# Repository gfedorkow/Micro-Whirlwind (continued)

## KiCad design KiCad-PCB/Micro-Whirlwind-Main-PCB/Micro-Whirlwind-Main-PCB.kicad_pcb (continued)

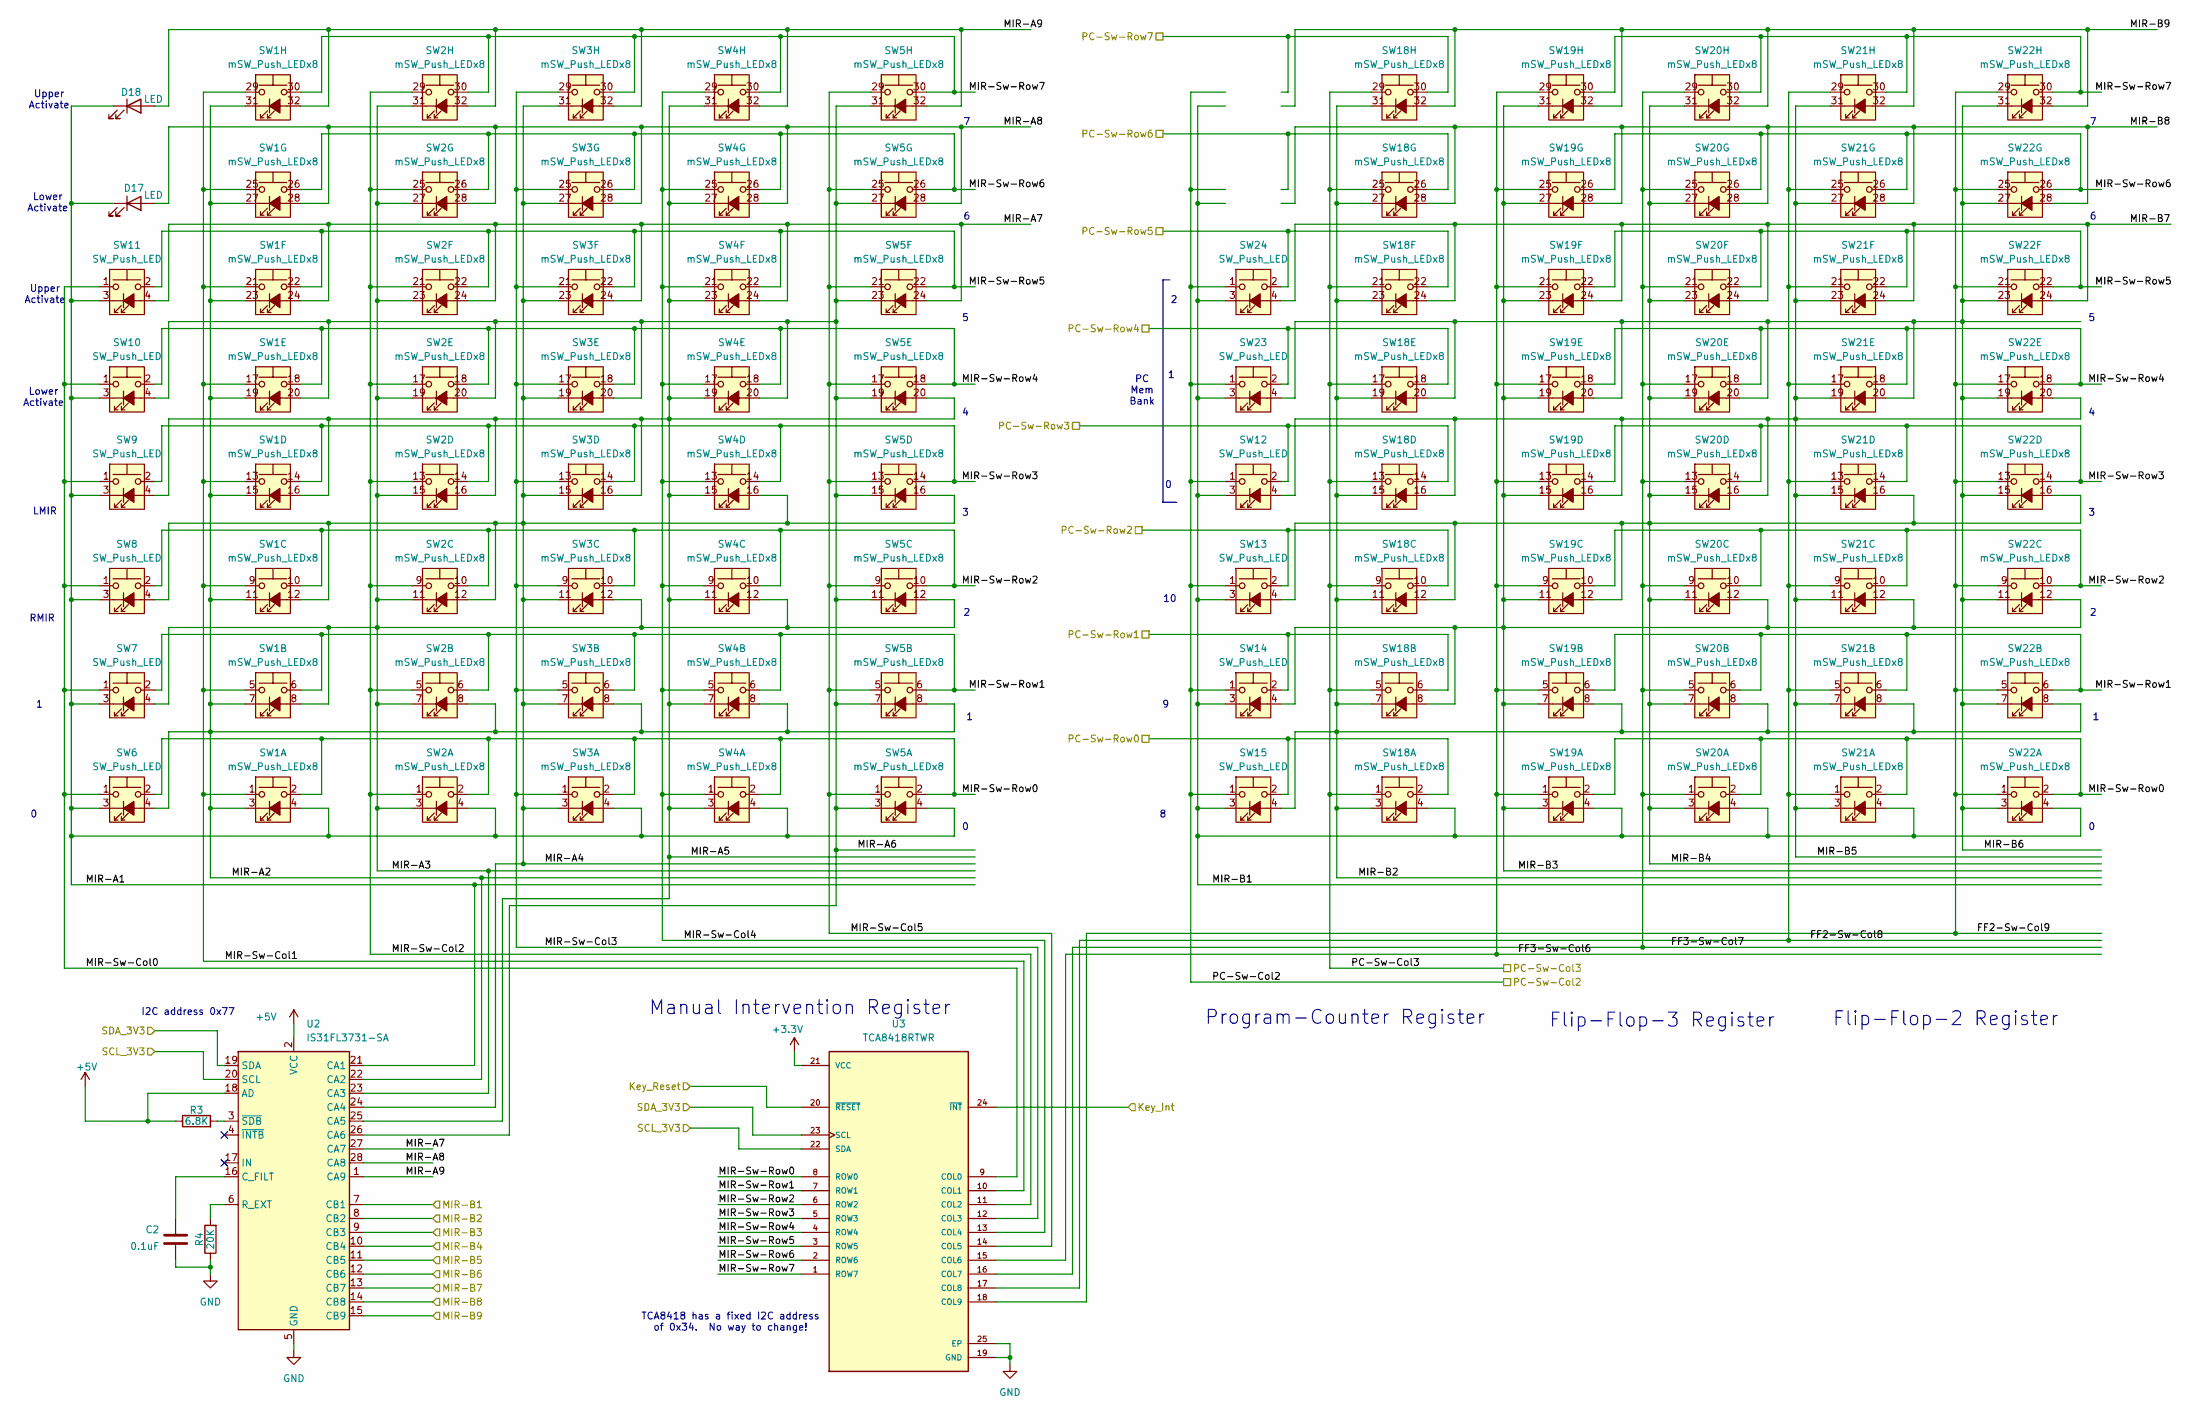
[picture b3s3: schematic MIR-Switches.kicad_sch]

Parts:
C2: 0.1uF; Null-FootPrint
D17, D18: LED; LED_D3.0mm_panel_cut
R3: 6.8K; Null-FootPrint
R4: 20K; Null-FootPrint
SW1, SW2, SW3, SW4, SW5, SW18, SW19, SW20, SW21, SW22: mSW_Push_LEDx8; Null-FootPrint
SW6, SW7, SW8, SW9, SW12, SW13, SW14, SW15, SW23, SW24: SW_Push_LED; Null-FootPrint
SW10, SW11: SW_Push_LED; ILS-TB-140-SW_PUSH_LED_round_panel
U2: IS31FL3731-SA; Null-FootPrint
U3: TCA8418RTWR; Null-FootPrint; PARTREV G

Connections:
+3.3V: U3.21 (VCC); also elsewhere on the board
+5V: R3.1, U2.2 (VCC), U2.18 (AD); also elsewhere on the board
/Execution-Control/PC-Sw-Row0: SW15.2, SW18.2 (SB); also elsewhere on the board
/Execution-Control/PC-Sw-Row1: SW14.2, SW18.6 (SB); also elsewhere on the board
/Execution-Control/PC-Sw-Row2: SW13.2, SW18.10 (SB); also elsewhere on the board
/Execution-Control/PC-Sw-Row3: SW12.2, SW18.14 (SB); also elsewhere on the board
/Execution-Control/PC-Sw-Row4: SW18.18 (SB), SW23.2; also elsewhere on the board
/Execution-Control/PC-Sw-Row5: SW18.22 (SB), SW24.2; also elsewhere on the board
/Execution-Control/PC-Sw-Row6: SW18.26 (SB); also elsewhere on the board
/Execution-Control/PC-Sw-Row7: SW18.30 (SB); also elsewhere on the board
/Key_Interrupt: U3.24 (~INT); also elsewhere on the board
/Key_Reset: U3.20 (~RESET); also elsewhere on the board
/MIR-Switches/FF2-Sw-Col8: SW21.1 (SA), SW21.5 (SA), SW21.9 (SA), SW21.13 (SA), SW21.17 (SA), SW21.21 (SA), SW21.25 (SA), SW21.29 (SA), U3.17 (COL8)
/MIR-Switches/FF2-Sw-Col9: SW22.1 (SA), SW22.5 (SA), SW22.9 (SA), SW22.13 (SA), SW22.17 (SA), SW22.21 (SA), SW22.25 (SA), SW22.29 (SA), U3.18 (COL9)
/MIR-Switches/FF3-Sw-Col6: SW19.1 (SA), SW19.5 (SA), SW19.9 (SA), SW19.13 (SA), SW19.17 (SA), SW19.21 (SA), SW19.25 (SA), SW19.29 (SA), U3.15 (COL6)
/MIR-Switches/FF3-Sw-Col7: SW20.1 (SA), SW20.5 (SA), SW20.9 (SA), SW20.13 (SA), SW20.17 (SA), SW20.21 (SA), SW20.25 (SA), SW20.29 (SA), U3.16 (COL7)
/MIR-Switches/MIR-A1: D17.1 (K), D18.1 (K), SW1.4 (A), SW2.4 (A), SW3.4 (A), SW4.4 (A), SW5.4 (A), SW6.3 (K), SW7.3 (K), SW8.3 (K), SW9.3 (K), SW10.3 (K), SW11.3 (K), U2.21 (CA1)
/MIR-Switches/MIR-A2: SW1.3 (K), SW1.7 (K), SW1.11 (K), SW1.15 (K), SW1.19 (K), SW1.23 (K), SW1.27 (K), SW1.31 (K), SW2.8 (A), SW3.8 (A), SW4.8 (A), SW5.8 (A), SW6.4 (A), U2.22 (CA2)
/MIR-Switches/MIR-A3: SW1.8 (A), SW2.3 (K), SW2.7 (K), SW2.11 (K), SW2.15 (K), SW2.19 (K), SW2.23 (K), SW2.27 (K), SW2.31 (K), SW3.12 (A), SW4.12 (A), SW5.12 (A), SW7.4 (A), U2.23 (CA3)
/MIR-Switches/MIR-A4: SW1.12 (A), SW2.12 (A), SW3.3 (K), SW3.7 (K), SW3.11 (K), SW3.15 (K), SW3.19 (K), SW3.23 (K), SW3.27 (K), SW3.31 (K), SW4.16 (A), SW5.16 (A), SW8.4 (A), U2.24 (CA4)
/MIR-Switches/MIR-A5: SW1.16 (A), SW2.16 (A), SW3.16 (A), SW4.3 (K), SW4.7 (K), SW4.11 (K), SW4.15 (K), SW4.19 (K), SW4.23 (K), SW4.27 (K), SW4.31 (K), SW5.20 (A), SW9.4 (A), U2.25 (CA5)
/MIR-Switches/MIR-A6: SW1.20 (A), SW2.20 (A), SW3.20 (A), SW4.20 (A), SW5.3 (K), SW5.7 (K), SW5.11 (K), SW5.15 (K), SW5.19 (K), SW5.23 (K), SW5.27 (K), SW5.31 (K), SW10.4 (A), U2.26 (CA6)
/MIR-Switches/MIR-A7: SW1.24 (A), SW2.24 (A), SW3.24 (A), SW4.24 (A), SW5.24 (A), SW11.4 (A), U2.27 (CA7)
/MIR-Switches/MIR-A8: D17.2 (A), SW1.28 (A), SW2.28 (A), SW3.28 (A), SW4.28 (A), SW5.28 (A), U2.28 (CA8)
/MIR-Switches/MIR-A9: D18.2 (A), SW1.32 (A), SW2.32 (A), SW3.32 (A), SW4.32 (A), SW5.32 (A), U2.1 (CA9)
/MIR-Switches/MIR-B1: SW12.3 (K), SW13.3 (K), SW14.3 (K), SW15.3 (K), SW18.4 (A), SW19.4 (A), SW20.4 (A), SW21.4 (A), SW22.4 (A), SW23.3 (K), SW24.3 (K), U2.7 (CB1); also elsewhere on the board
/MIR-Switches/MIR-B2: SW15.4 (A), SW18.3 (K), SW18.7 (K), SW18.11 (K), SW18.15 (K), SW18.19 (K), SW18.23 (K), SW18.27 (K), SW18.31 (K), SW19.8 (A), SW20.8 (A), SW21.8 (A), SW22.8 (A), U2.8 (CB2); also elsewhere on the board
/MIR-Switches/MIR-B3: SW14.4 (A), SW18.8 (A), SW19.3 (K), SW19.7 (K), SW19.11 (K), SW19.15 (K), SW19.19 (K), SW19.23 (K), SW19.27 (K), SW19.31 (K), SW20.12 (A), SW21.12 (A), SW22.12 (A), U2.9 (CB3); also elsewhere on the board
/MIR-Switches/MIR-B4: SW13.4 (A), SW18.12 (A), SW19.12 (A), SW20.3 (K), SW20.7 (K), SW20.11 (K), SW20.15 (K), SW20.19 (K), SW20.23 (K), SW20.27 (K), SW20.31 (K), SW21.16 (A), SW22.16 (A), U2.10 (CB4); also elsewhere on the board
/MIR-Switches/MIR-B5: SW12.4 (A), SW18.16 (A), SW19.16 (A), SW20.16 (A), SW21.3 (K), SW21.7 (K), SW21.11 (K), SW21.15 (K), SW21.19 (K), SW21.23 (K), SW21.27 (K), SW21.31 (K), SW22.20 (A), U2.11 (CB5); also elsewhere on the board
/MIR-Switches/MIR-B6: SW18.20 (A), SW19.20 (A), SW20.20 (A), SW21.20 (A), SW22.3 (K), SW22.7 (K), SW22.11 (K), SW22.15 (K), SW22.19 (K), SW22.23 (K), SW22.27 (K), SW22.31 (K), SW23.4 (A), U2.12 (CB6); also elsewhere on the board
/MIR-Switches/MIR-B7: SW18.24 (A), SW19.24 (A), SW20.24 (A), SW21.24 (A), SW22.24 (A), SW24.4 (A), U2.13 (CB7); also elsewhere on the board
/MIR-Switches/MIR-B8: SW18.28 (A), SW19.28 (A), SW20.28 (A), SW21.28 (A), SW22.28 (A), U2.14 (CB8); also elsewhere on the board
/MIR-Switches/MIR-B9: SW18.32 (A), SW19.32 (A), SW20.32 (A), SW21.32 (A), SW22.32 (A), U2.15 (CB9); also elsewhere on the board
/MIR-Switches/MIR-Sw-Col0: SW6.1, SW7.1, SW8.1, SW9.1, SW10.1, SW11.1, U3.9 (COL0)
/MIR-Switches/MIR-Sw-Col1: SW1.1 (SA), SW1.5 (SA), SW1.9 (SA), SW1.13 (SA), SW1.17 (SA), SW1.21 (SA), SW1.25 (SA), SW1.29 (SA), U3.10 (COL1)
/MIR-Switches/MIR-Sw-Col2: SW2.1 (SA), SW2.5 (SA), SW2.9 (SA), SW2.13 (SA), SW2.17 (SA), SW2.21 (SA), SW2.25 (SA), SW2.29 (SA), U3.11 (COL2)
/MIR-Switches/MIR-Sw-Col3: SW3.1 (SA), SW3.5 (SA), SW3.9 (SA), SW3.13 (SA), SW3.17 (SA), SW3.21 (SA), SW3.25 (SA), SW3.29 (SA), U3.12 (COL3)
/MIR-Switches/MIR-Sw-Col4: SW4.1 (SA), SW4.5 (SA), SW4.9 (SA), SW4.13 (SA), SW4.17 (SA), SW4.21 (SA), SW4.25 (SA), SW4.29 (SA), U3.13 (COL4)
/MIR-Switches/MIR-Sw-Col5: SW5.1 (SA), SW5.5 (SA), SW5.9 (SA), SW5.13 (SA), SW5.17 (SA), SW5.21 (SA), SW5.25 (SA), SW5.29 (SA), U3.14 (COL5)
/MIR-Switches/MIR-Sw-Row0: SW1.2 (SB), SW2.2 (SB), SW3.2 (SB), SW4.2 (SB), SW5.2 (SB), SW6.2, SW19.2 (SB), SW20.2 (SB), SW21.2 (SB), SW22.2 (SB), U3.8 (ROW0)
/MIR-Switches/MIR-Sw-Row1: SW1.6 (SB), SW2.6 (SB), SW3.6 (SB), SW4.6 (SB), SW5.6 (SB), SW7.2, SW19.6 (SB), SW20.6 (SB), SW21.6 (SB), SW22.6 (SB), U3.7 (ROW1)
/MIR-Switches/MIR-Sw-Row2: SW1.10 (SB), SW2.10 (SB), SW3.10 (SB), SW4.10 (SB), SW5.10 (SB), SW8.2, SW19.10 (SB), SW20.10 (SB), SW21.10 (SB), SW22.10 (SB), U3.6 (ROW2)
/MIR-Switches/MIR-Sw-Row3: SW1.14 (SB), SW2.14 (SB), SW3.14 (SB), SW4.14 (SB), SW5.14 (SB), SW9.2, SW19.14 (SB), SW20.14 (SB), SW21.14 (SB), SW22.14 (SB), U3.5 (ROW3)
/MIR-Switches/MIR-Sw-Row4: SW1.18 (SB), SW2.18 (SB), SW3.18 (SB), SW4.18 (SB), SW5.18 (SB), SW10.2, SW19.18 (SB), SW20.18 (SB), SW21.18 (SB), SW22.18 (SB), U3.4 (ROW4)
/MIR-Switches/MIR-Sw-Row5: SW1.22 (SB), SW2.22 (SB), SW3.22 (SB), SW4.22 (SB), SW5.22 (SB), SW11.2, SW19.22 (SB), SW20.22 (SB), SW21.22 (SB), SW22.22 (SB), U3.3 (ROW5)
/MIR-Switches/MIR-Sw-Row6: SW1.26 (SB), SW2.26 (SB), SW3.26 (SB), SW4.26 (SB), SW5.26 (SB), SW19.26 (SB), SW20.26 (SB), SW21.26 (SB), SW22.26 (SB), U3.2 (ROW6)
/MIR-Switches/MIR-Sw-Row7: SW1.30 (SB), SW2.30 (SB), SW3.30 (SB), SW4.30 (SB), SW5.30 (SB), SW19.30 (SB), SW20.30 (SB), SW21.30 (SB), SW22.30 (SB), U3.1 (ROW7)
/MIR-Switches/PC-Sw-Col2: SW12.1, SW13.1, SW14.1, SW15.1, SW23.1, SW24.1; also elsewhere on the board
/MIR-Switches/PC-Sw-Col3: SW18.1 (SA), SW18.5 (SA), SW18.9 (SA), SW18.13 (SA), SW18.17 (SA), SW18.21 (SA), SW18.25 (SA), SW18.29 (SA); also elsewhere on the board
/SCL_3V3: U2.20 (SCL), U3.22 (SDA); also elsewhere on the board
/SDA_3V3: U2.19 (SDA), U3.23 (SCL); also elsewhere on the board
GND: C2.2, R4.1, U2.5 (GND), U3.19 (GND), U3.25 (EP); also elsewhere on the board
unnamed: C2.1, U2.16 (C_FILT)
unnamed: R4.2, U2.6 (R_EXT)
unnamed: R3.2, U2.3 (~SDB)

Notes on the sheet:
Flip-Flop-2 Register
RMIR
I2C address 0x77
Upper Activate
Flip-Flop-3 Register
PC Mem Bank
Lower Activate
LMIR
TCA8418 has a fixed I2C address of 0x34. No way to change!
Manual Intervention Register
Program-Counter Register

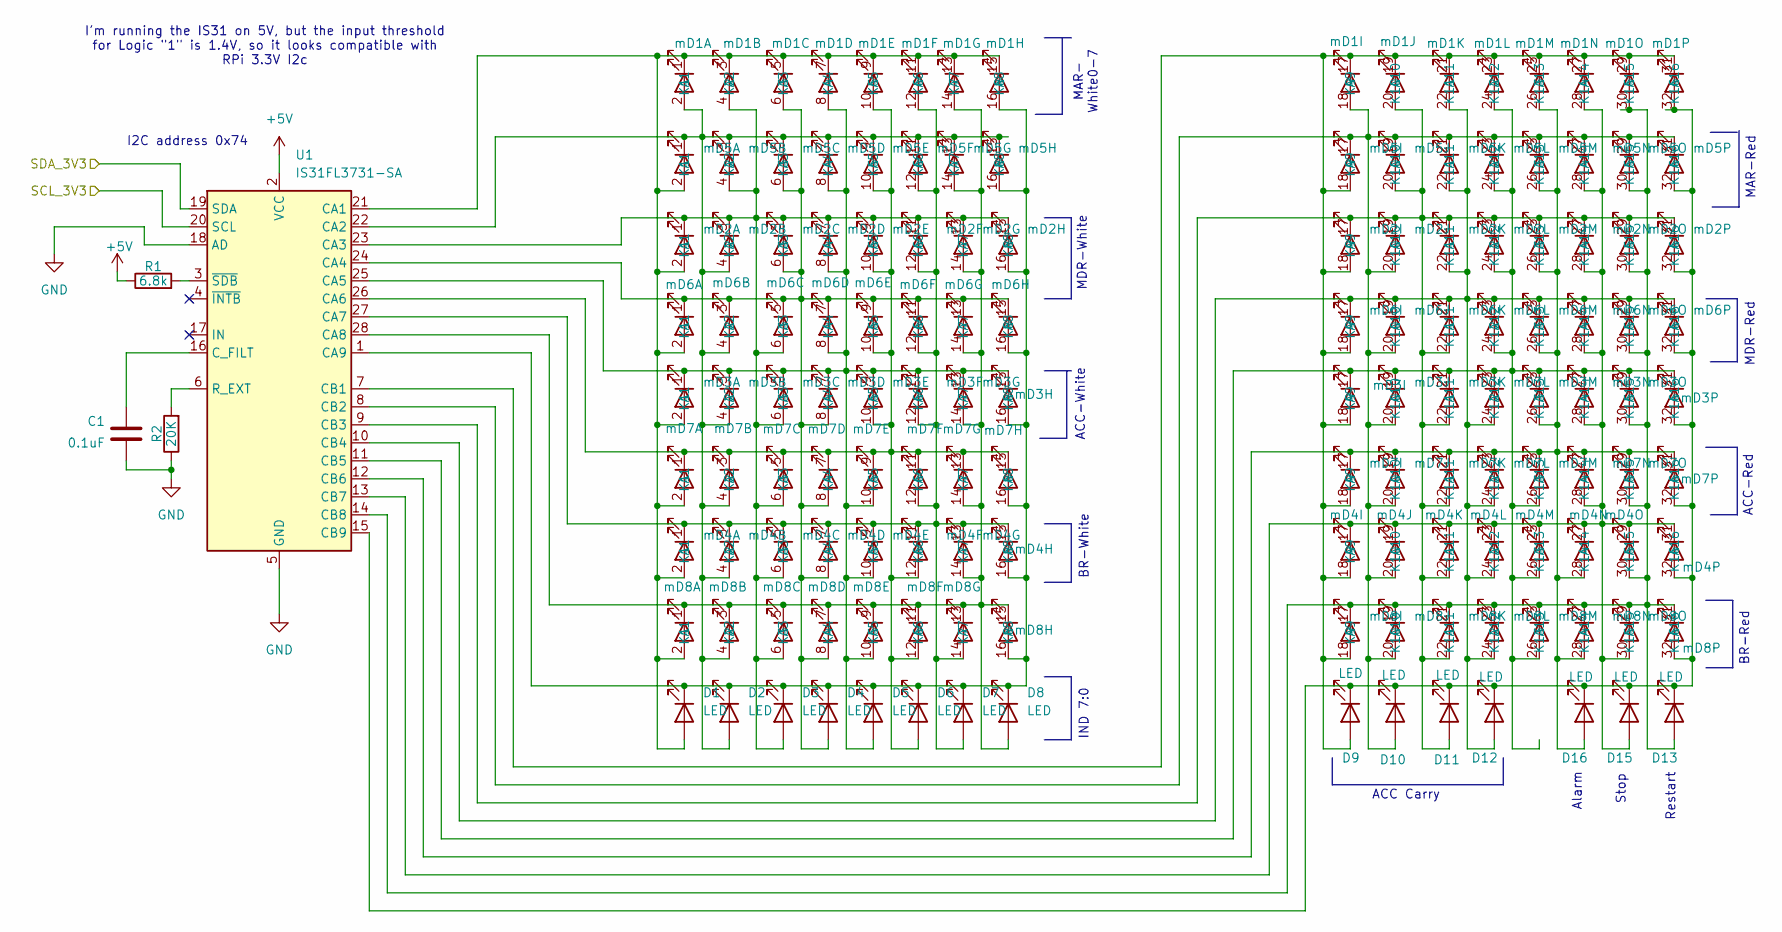
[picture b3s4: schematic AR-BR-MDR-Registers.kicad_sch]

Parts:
C1: 0.1uF; C_Rect_L7.0mm_W2.5mm_P5.00mm
D1, D2, D3, D4, D5, D6, D7, D8, D9, D10, D11, D12, D13, D15: LED; LED_D3.0mm
D16: LED; LED_D5.0mm
R1: 6.8k; SM-1206B
R2: 20K; SM-1206B
U1: IS31FL3731-SA; SSOP-28_5.3x10.2mm_P0.65mm
mD1, mD2, mD3, mD4, mD5, mD6, mD7, mD8: LED_D3.0mm_16x_bank

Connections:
+5V: R1.1, U1.2 (VCC); also elsewhere on the board
/SCL_3V3: U1.20 (SCL); also elsewhere on the board
/SDA_3V3: U1.19 (SDA); also elsewhere on the board
GND: C1.2, R2.1, U1.5 (GND), U1.18 (AD); also elsewhere on the board
unnamed: D1.2 (A), U1.21 (CA1), mD1.1 (K1), mD1.3 (K2), mD1.5 (K3), mD1.7 (K4), mD1.9 (K5), mD1.11 (K6), mD1.13 (K7), mD1.15 (K8), mD2.2 (A1), mD3.2 (A1), mD4.2 (A1), mD5.2 (A1), mD6.2 (A1), mD7.2 (A1), mD8.2 (A1)
unnamed: D1.1 (K), D2.1 (K), D3.1 (K), D4.1 (K), D5.1 (K), D6.1 (K), D7.1 (K), D8.1 (K), U1.1 (CA9), mD1.16 (A8), mD2.16 (A8), mD3.16 (A8), mD4.16 (A8), mD5.16 (A8), mD6.16 (A8), mD7.16 (A8), mD8.16 (A8)
unnamed: D2.2 (A), U1.22 (CA2), mD1.2 (A1), mD2.4 (A2), mD3.4 (A2), mD4.4 (A2), mD5.1 (K1), mD5.3 (K2), mD5.5 (K3), mD5.7 (K4), mD5.9 (K5), mD5.11 (K6), mD5.13 (K7), mD5.15 (K8), mD6.4 (A2), mD7.4 (A2), mD8.4 (A2)
unnamed: D3.2 (A), U1.23 (CA3), mD1.4 (A2), mD2.1 (K1), mD2.3 (K2), mD2.5 (K3), mD2.7 (K4), mD2.9 (K5), mD2.11 (K6), mD2.13 (K7), mD2.15 (K8), mD3.6 (A3), mD4.6 (A3), mD5.4 (A2), mD6.6 (A3), mD7.6 (A3), mD8.6 (A3)
unnamed: D4.2 (A), U1.24 (CA4), mD1.6 (A3), mD2.6 (A3), mD3.8 (A4), mD4.8 (A4), mD5.6 (A3), mD6.1 (K1), mD6.3 (K2), mD6.5 (K3), mD6.7 (K4), mD6.9 (K5), mD6.11 (K6), mD6.13 (K7), mD6.15 (K8), mD7.8 (A4), mD8.8 (A4)
unnamed: D5.2 (A), U1.25 (CA5), mD1.8 (A4), mD2.8 (A4), mD3.1 (K1), mD3.3 (K2), mD3.5 (K3), mD3.7 (K4), mD3.9 (K5), mD3.11 (K6), mD3.13 (K7), mD3.15 (K8), mD4.10 (A5), mD5.8 (A4), mD6.8 (A4), mD7.10 (A5), mD8.10 (A5)
unnamed: D6.2 (A), U1.26 (CA6), mD1.10 (A5), mD2.10 (A5), mD3.10 (A5), mD4.12 (A6), mD5.10 (A5), mD6.10 (A5), mD7.1 (K1), mD7.3 (K2), mD7.5 (K3), mD7.7 (K4), mD7.9 (K5), mD7.11 (K6), mD7.13 (K7), mD7.15 (K8), mD8.12 (A6)
unnamed: D7.2 (A), U1.27 (CA7), mD1.12 (A6), mD2.12 (A6), mD3.12 (A6), mD4.1 (K1), mD4.3 (K2), mD4.5 (K3), mD4.7 (K4), mD4.9 (K5), mD4.11 (K6), mD4.13 (K7), mD4.15 (K8), mD5.12 (A6), mD6.12 (A6), mD7.12 (A6), mD8.14 (A7)
unnamed: D8.2 (A), U1.28 (CA8), mD1.14 (A7), mD2.14 (A7), mD3.14 (A7), mD4.14 (A7), mD5.14 (A7), mD6.14 (A7), mD7.14 (A7), mD8.1 (K1), mD8.3 (K2), mD8.5 (K3), mD8.7 (K4), mD8.9 (K5), mD8.11 (K6), mD8.13 (K7), mD8.15 (K8)
unnamed: D9.2 (A), U1.7 (CB1), mD1.17 (K9), mD1.19 (K10), mD1.21 (K11), mD1.23 (K12), mD1.25 (K13), mD1.27 (K14), mD1.29 (K15), mD1.31 (K16), mD2.18 (A9), mD3.18 (A9), mD4.18 (A9), mD5.18 (A9), mD6.18 (A9), mD7.18 (A9), mD8.18 (A9)
unnamed: D10.2 (A), U1.8 (CB2), mD1.18 (A9), mD2.20 (A10), mD3.20 (A10), mD4.20 (A10), mD5.17 (K9), mD5.19 (K10), mD5.21 (K11), mD5.23 (K12), mD5.25 (K13), mD5.27 (K14), mD5.29 (K15), mD5.31 (K16), mD6.20 (A10), mD7.20 (A10), mD8.20 (A10)
unnamed: D9.1 (K), D10.1 (K), D11.1 (K), D12.1 (K), D13.1 (K), D15.1 (K), D16.1 (K), U1.15 (CB9), mD1.32 (A16), mD2.32 (A16), mD3.32 (A16), mD4.32 (A16), mD5.32 (A16), mD6.32 (A16), mD7.32 (A16), mD8.32 (A16)
unnamed: D11.2 (A), U1.9 (CB3), mD1.20 (A10), mD2.17 (K9), mD2.19 (K10), mD2.21 (K11), mD2.23 (K12), mD2.25 (K13), mD2.27 (K14), mD2.29 (K15), mD2.31 (K16), mD3.22 (A11), mD4.22 (A11), mD5.20 (A10), mD6.22 (A11), mD7.22 (A11), mD8.22 (A11)
unnamed: D12.2 (A), U1.10 (CB4), mD1.22 (A11), mD2.22 (A11), mD3.24 (A12), mD4.24 (A12), mD5.22 (A11), mD6.17 (K9), mD6.19 (K10), mD6.21 (K11), mD6.23 (K12), mD6.25 (K13), mD6.27 (K14), mD6.29 (K15), mD6.31 (K16), mD7.24 (A12), mD8.24 (A12)
unnamed: D13.2 (A), U1.14 (CB8), mD1.30 (A15), mD2.30 (A15), mD3.30 (A15), mD4.30 (A15), mD5.30 (A15), mD6.30 (A15), mD7.30 (A15), mD8.17 (K9), mD8.19 (K10), mD8.21 (K11), mD8.23 (K12), mD8.25 (K13), mD8.27 (K14), mD8.29 (K15), mD8.31 (K16)
unnamed: D15.2 (A), U1.13 (CB7), mD1.28 (A14), mD2.28 (A14), mD3.28 (A14), mD4.17 (K9), mD4.19 (K10), mD4.21 (K11), mD4.23 (K12), mD4.25 (K13), mD4.27 (K14), mD4.29 (K15), mD4.31 (K16), mD5.28 (A14), mD6.28 (A14), mD7.28 (A14), mD8.30 (A15)
unnamed: D16.2 (A), U1.12 (CB6), mD1.26 (A13), mD2.26 (A13), mD3.26 (A13), mD4.28 (A14), mD5.26 (A13), mD6.26 (A13), mD7.17 (K9), mD7.19 (K10), mD7.21 (K11), mD7.23 (K12), mD7.25 (K13), mD7.27 (K14), mD7.29 (K15), mD7.31 (K16), mD8.28 (A14)
unnamed: U1.11 (CB5), mD1.24 (A12), mD2.24 (A12), mD3.17 (K9), mD3.19 (K10), mD3.21 (K11), mD3.23 (K12), mD3.25 (K13), mD3.27 (K14), mD3.29 (K15), mD3.31 (K16), mD4.26 (A13), mD5.24 (A12), mD6.24 (A12), mD7.26 (A13), mD8.26 (A13)
unnamed: C1.1, U1.16 (C_FILT)
unnamed: R2.2, U1.6 (R_EXT)
unnamed: R1.2, U1.3 (~SDB)

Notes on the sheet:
BR-Red
MDR-White
Alarm
MAR-Red
IND 7:0
I'm running the IS31 on 5V, but the input threshold for Logic "1" is 1.4V, so it looks compatible with RPi 3.3V I2c
MAR- White0-7
ACC Carry
Stop
Restart
ACC-Red
BR-White
MDR-Red
I2C address 0x74
ACC-White

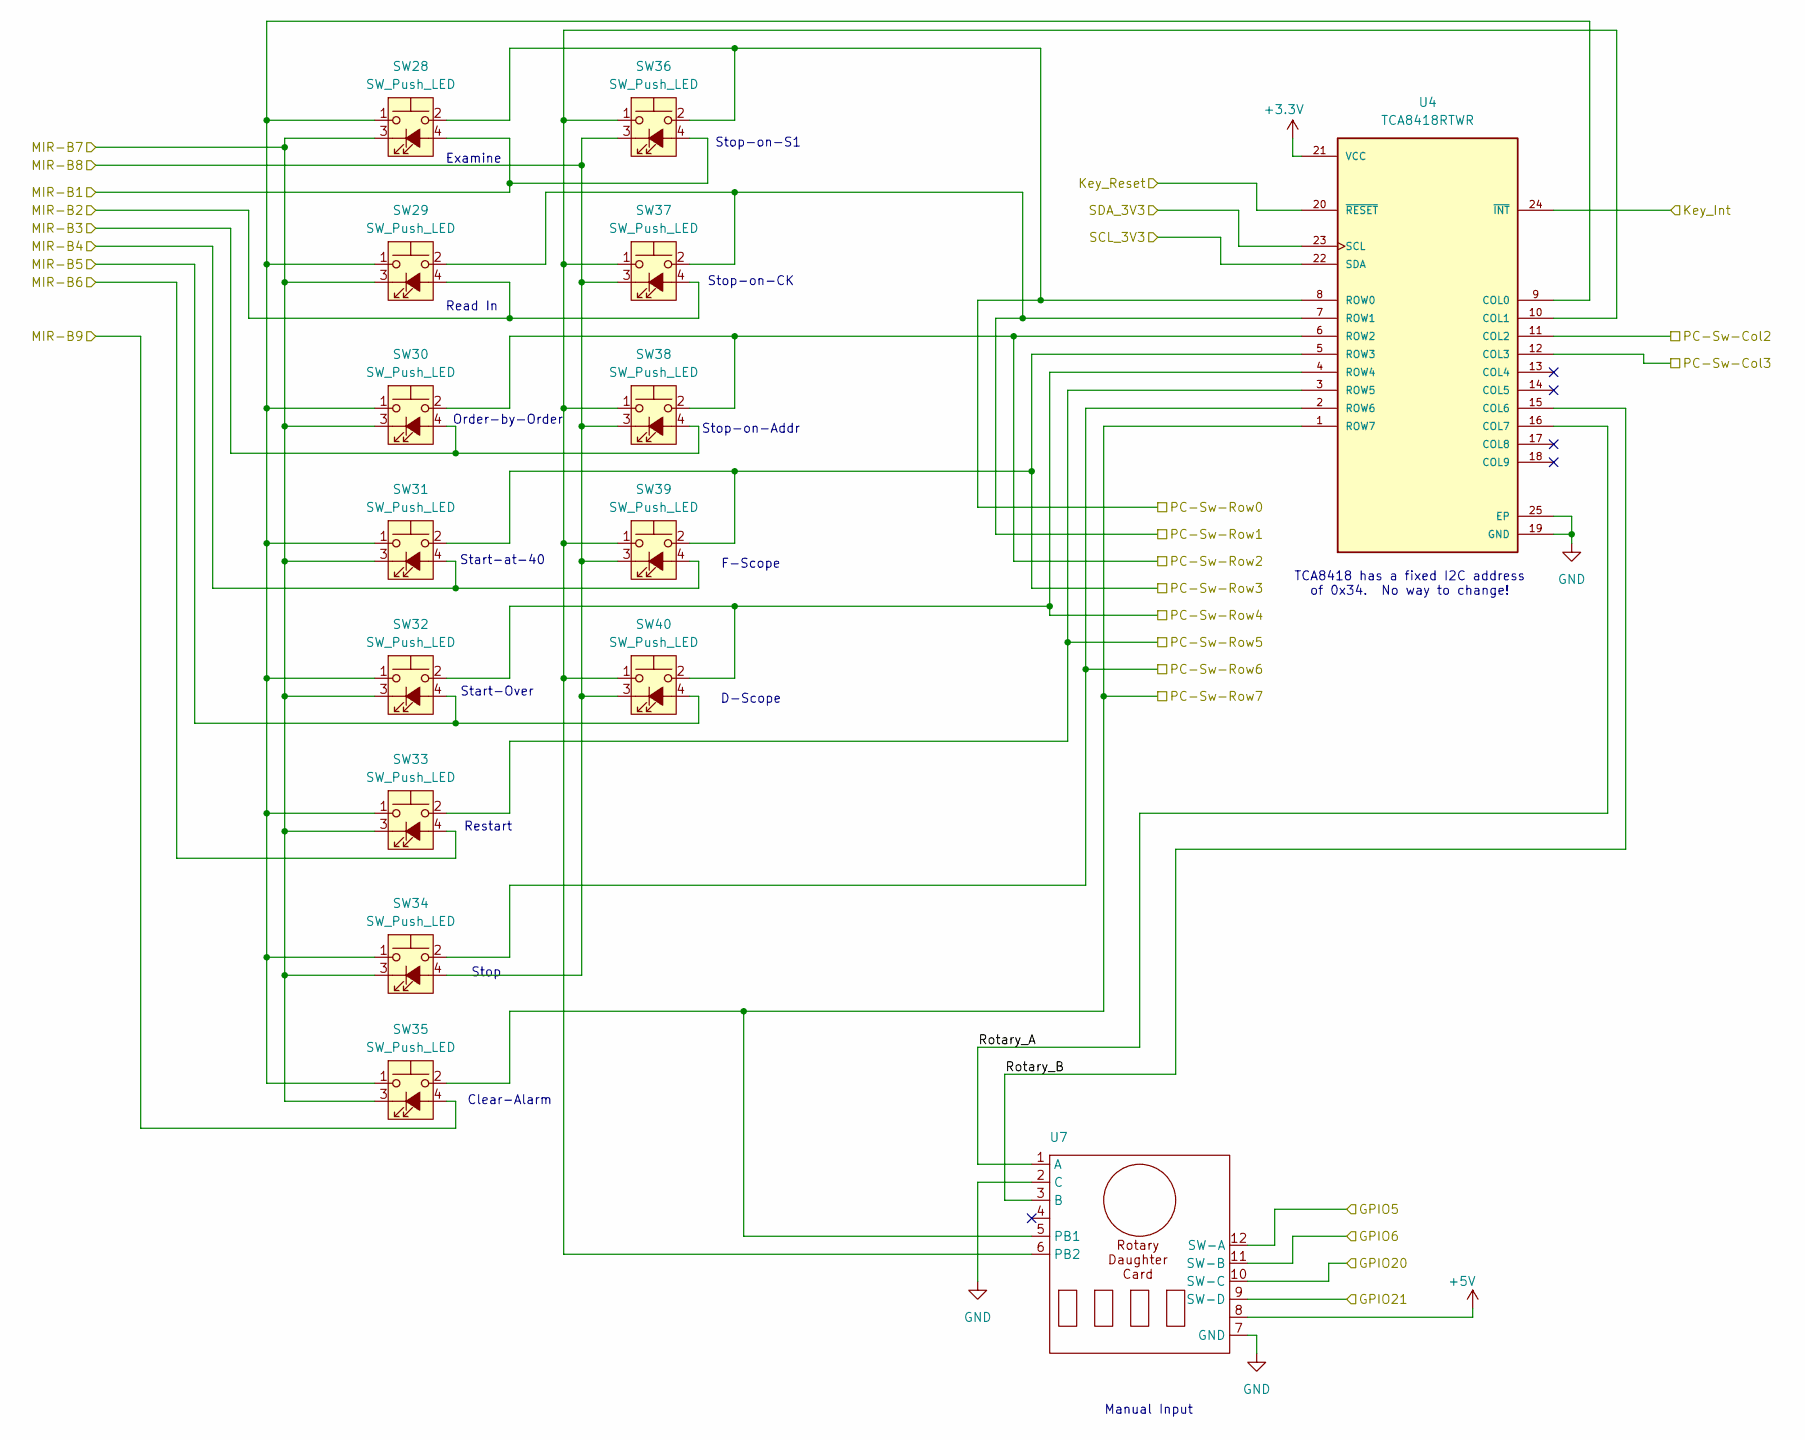
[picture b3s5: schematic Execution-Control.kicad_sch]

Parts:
SW28, SW29, SW30, SW31, SW32, SW33, SW34, SW35: SW_Push_LED; ILS-TB-140-SW_PUSH_LED_round
SW36, SW37, SW38, SW39, SW40: SW_Push_LED; ILS-TB-140-SW_PUSH_and_LED_6mm
U4: TCA8418RTWR; QFN50P400X400X80-25N; PARTREV G
U7: Rotary-Daughter-PCB

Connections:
+3.3V: U4.21 (VCC); also elsewhere on the board
+5V: U7.8; also elsewhere on the board
/Analog-Scope_Interface/GPIO5: U7.12 (SW-A); also elsewhere on the board
/Analog-Scope_Interface/GPIO6: U7.11 (SW-B); also elsewhere on the board
/Analog-Scope_Interface/GPIO20: U7.10 (SW-C); also elsewhere on the board
/Analog-Scope_Interface/GPIO21: U7.9 (SW-D); also elsewhere on the board
/Execution-Control/PC-Sw-Row0: SW28.2, SW36.2, U4.8 (ROW0); also elsewhere on the board
/Execution-Control/PC-Sw-Row1: SW29.2, SW37.2, U4.7 (ROW1); also elsewhere on the board
/Execution-Control/PC-Sw-Row2: SW30.2, SW38.2, U4.6 (ROW2); also elsewhere on the board
/Execution-Control/PC-Sw-Row3: SW31.2, SW39.2, U4.5 (ROW3); also elsewhere on the board
/Execution-Control/PC-Sw-Row4: SW32.2, SW40.2, U4.4 (ROW4); also elsewhere on the board
/Execution-Control/PC-Sw-Row5: SW33.2, U4.3 (ROW5); also elsewhere on the board
/Execution-Control/PC-Sw-Row6: SW34.2, U4.2 (ROW6); also elsewhere on the board
/Execution-Control/PC-Sw-Row7: SW35.2, U4.1 (ROW7), U7.5 (PB1); also elsewhere on the board
/Execution-Control/Rotary_A: U4.16 (COL7), U7.1 (A)
/Execution-Control/Rotary_B: U4.15 (COL6), U7.3 (B)
/Execution-Control/SCL_3V3: U4.22 (SDA); also elsewhere on the board
/Execution-Control/SDA_3V3: U4.23 (SCL); also elsewhere on the board
/Key_Interrupt: U4.24 (~INT); also elsewhere on the board
/Key_Reset: U4.20 (~RESET); also elsewhere on the board
/MIR-Switches/MIR-B1: SW28.4 (A), SW36.4 (A); also elsewhere on the board
/MIR-Switches/MIR-B2: SW29.4 (A), SW37.4 (A); also elsewhere on the board
/MIR-Switches/MIR-B3: SW30.4 (A), SW38.4 (A); also elsewhere on the board
/MIR-Switches/MIR-B4: SW31.4 (A), SW39.4 (A); also elsewhere on the board
/MIR-Switches/MIR-B5: SW32.4 (A), SW40.4 (A); also elsewhere on the board
/MIR-Switches/MIR-B6: SW33.4 (A); also elsewhere on the board
/MIR-Switches/MIR-B7: SW28.3 (K), SW29.3 (K), SW30.3 (K), SW31.3 (K), SW32.3 (K), SW33.3 (K), SW34.3 (K), SW35.3 (K); also elsewhere on the board
/MIR-Switches/MIR-B8: SW34.4 (A), SW36.3 (K), SW37.3 (K), SW38.3 (K), SW39.3 (K), SW40.3 (K); also elsewhere on the board
/MIR-Switches/MIR-B9: SW35.4 (A); also elsewhere on the board
/MIR-Switches/PC-Sw-Col2: U4.11 (COL2); also elsewhere on the board
/MIR-Switches/PC-Sw-Col3: U4.12 (COL3); also elsewhere on the board
GND: U4.19 (GND), U4.25 (EP), U7.2 (C), U7.7 (GND); also elsewhere on the board
unnamed: SW28.1, SW29.1, SW30.1, SW31.1, SW32.1, SW33.1, SW34.1, SW35.1, U4.9 (COL0)
unnamed: SW36.1, SW37.1, SW38.1, SW39.1, SW40.1, U4.10 (COL1), U7.6 (PB2)

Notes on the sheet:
F-Scope
Manual Input
Start-Over
Stop-on-S1
Read In
Start-at-40
TCA8418 has a fixed I2C address of 0x34. No way to change!
Stop-on-Addr
Stop-on-CK
Stop
Clear-Alarm
Examine
Restart
Order-by-Order
D-Scope

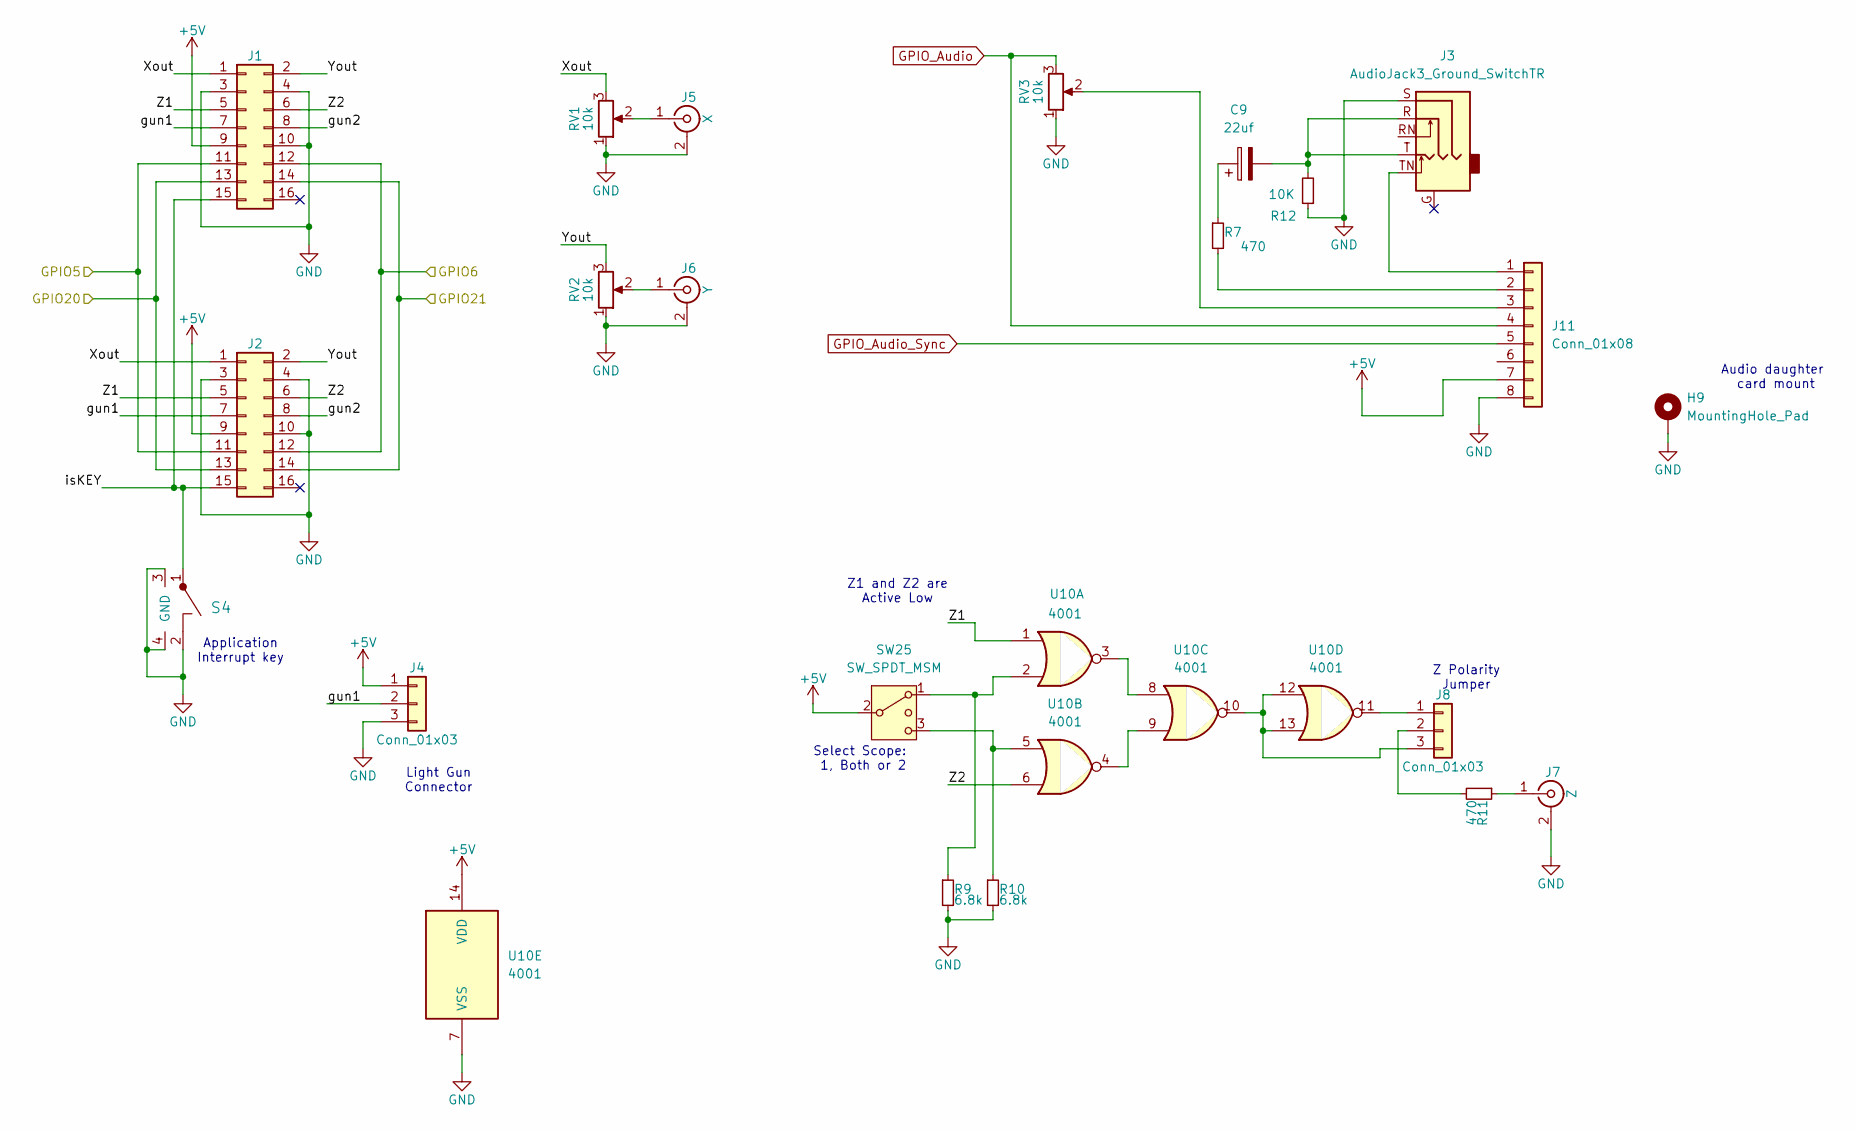
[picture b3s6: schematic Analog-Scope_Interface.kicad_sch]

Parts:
C9: 22uf; CP_Radial_D5.0mm_P2.50mm
H9: MountingHole_Pad; MountingHole_3.2mm_M3_DIN965_Pad_TopBottom
J1: Conn_02x08_Odd_Even; IDC-Header_2x08_P2.54mm_Horizontal
J2: Conn_02x08_Odd_Even; IDC-Header_2x08_P2.54mm_Vertical
J3: AudioJack3_Ground_SwitchTR; Jack_3.5mm_CUI_SJ1-3535NG_Horizontal
J4, J8: Conn_01x03; PSS_3
J5: X; CUI_RCJ-041
J6: Y; CUI_RCJ-041
J7: Z; CUI_RCJ-041
J11: Conn_01x08; PinHeader_1x08_P2.54mm_Vertical
R7, R11: 470; SM-1206B
R9, R10: 6.8k; SM-1206B
R12: 10K; SM-1206B
RV1, RV2, RV3: 10k; Potentiometer_Bourns_PTV09A-2_Single_Horizontal
S4: RA_Push; SW_KSA0V311LFTR_CNK-RA-pushbutton
SW25: SW_SPDT_MSM; SPDT-Toggle-Right-Angle
U10: 4001; SOIC-14_3.9x8.7mm_P1.27mm

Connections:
+5V: J1.9, J2.9, J4.1, J11.7, SW25.2 (3), U10.14 (VDD); also elsewhere on the board
/Analog-Scope_Interface/GPIO5: J1.11, J2.11; also elsewhere on the board
/Analog-Scope_Interface/GPIO6: J1.12, J2.12; also elsewhere on the board
/Analog-Scope_Interface/GPIO20: J1.13, J2.13; also elsewhere on the board
/Analog-Scope_Interface/GPIO21: J1.14, J2.14; also elsewhere on the board
/Analog-Scope_Interface/Xout: J1.1, J2.1, RV1.3
/Analog-Scope_Interface/Yout: J1.2, J2.2, RV2.3
/Analog-Scope_Interface/Z1: J1.5, J2.5, U10.1
/Analog-Scope_Interface/Z2: J1.6, J2.6, U10.6
/Analog-Scope_Interface/gun1: J1.7, J2.7, J4.2
/Analog-Scope_Interface/gun2: J1.8, J2.8
/Analog-Scope_Interface/isKEY: J1.15, J2.15, S4.1
GND: H9.1, J1.3, J1.4, J1.10, J2.3, J2.4, J2.10, J3.S, J4.3, J5.2 (Ext), J6.2 (Ext), J7.2 (Ext), J11.8, R9.2, R10.2, R12.1, RV1.1, RV2.1, RV3.1, S4.2, S4.3 (GND), S4.4, U10.7 (VSS); also elsewhere on the board
GPIO_Audio: J11.4, RV3.3
GPIO_Audio_Sync: J11.5
unnamed: C9.1, R7.1
unnamed: C9.2, J3.R, J3.T, R12.2
unnamed: J5.1 (In), RV1.2
unnamed: J6.1 (In), RV2.2
unnamed: J7.1 (In), R11.1
unnamed: J8.1, U10.11
unnamed: J8.2, R11.2
unnamed: J8.3, U10.10, U10.12, U10.13
unnamed: J3.TN, J11.1
unnamed: J11.2, R7.2
unnamed: J11.3, RV3.2
unnamed: R9.1, SW25.1, U10.2
unnamed: R10.1, SW25.3 (4), U10.5
unnamed: U10.3, U10.8
unnamed: U10.4, U10.9

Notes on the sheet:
Light Gun Connector
Z Polarity Jumper
Application Interrupt key
Z1 and Z2 are Active Low
Select Scope: 1, Both or 2
Audio daughter card mount
